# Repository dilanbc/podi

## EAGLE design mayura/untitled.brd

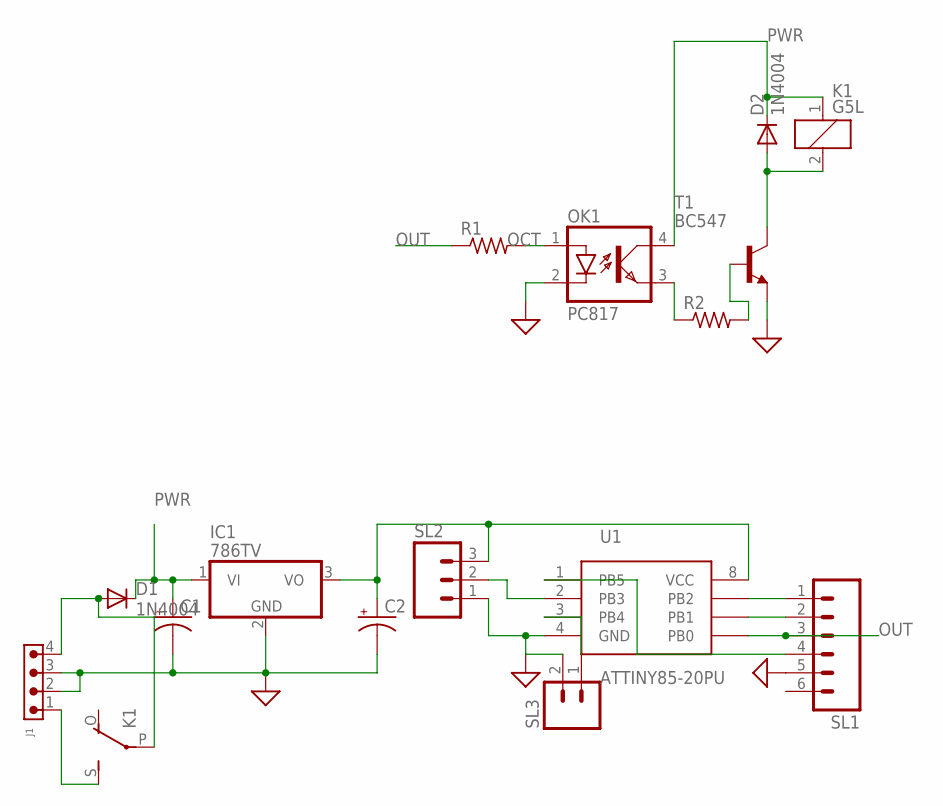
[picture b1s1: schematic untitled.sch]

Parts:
C1: CAPACITOR-PE5-10.5; E5-10,5
C2: CAPACITOR-PE2.5-5; E2,5-5
D1, D2: 1N4004; DO41-10
IC1: 786TV; TO220V
J1: 691305530004
K1: G5L; G5LE
OK1: PC817; DIL04
R1: R-US_0411/15; 0411/15
R2: R-US_0207/10; 0207/10
SL1: M06; 06P
SL2: M03; 03P
SL3: M02; 02P
T1: BC547; TO92
U1: ATTINY85-20PU; PDIP-8

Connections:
GND: C1.-, C2.-, IC1.2 (GND), J1.2, J1.3, OK1.2 (C), SL1.5, SL2.1, SL3.2, T1.1 (E), U1.4 (GND)
unnamed: D1.A, J1.4, K1.P
unnamed: SL1.1, U1.7 (PB2)
unnamed: C2.+, IC1.3 (VO), SL2.3, U1.8 (VCC)
unnamed: OK1.3 (EMIT), R2.1
unnamed: D2.A, K1.2, T1.3 (C)
unnamed: J1.1, K1.S
unnamed: R2.2, T1.2 (B)
unnamed: SL1.2, U1.6 (PB1)
unnamed: SL1.4, U1.1 (PB5)
unnamed: SL2.2, U1.2 (PB3)
unnamed: SL3.1, U1.3 (PB4)
OCT: OK1.1 (A), R1.2
OUT: R1.1, SL1.3, U1.5 (PB0)
PWR: C1.+, D1.C, D2.C, IC1.1 (VI), K1.1, OK1.4 (COL)

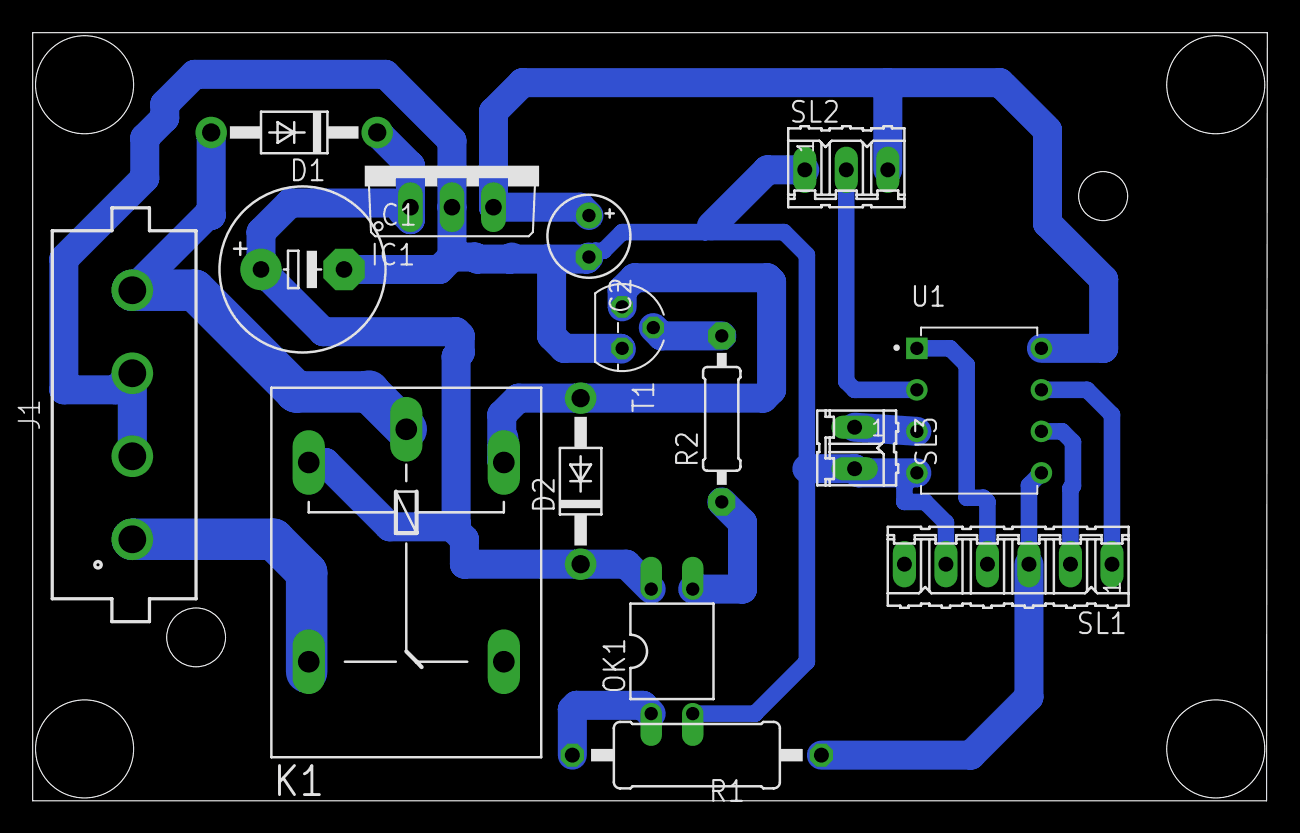
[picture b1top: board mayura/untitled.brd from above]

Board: 2 copper layers, 75.5 x 47.0 mm, 15 parts (0 on the bottom side), 15 nets.

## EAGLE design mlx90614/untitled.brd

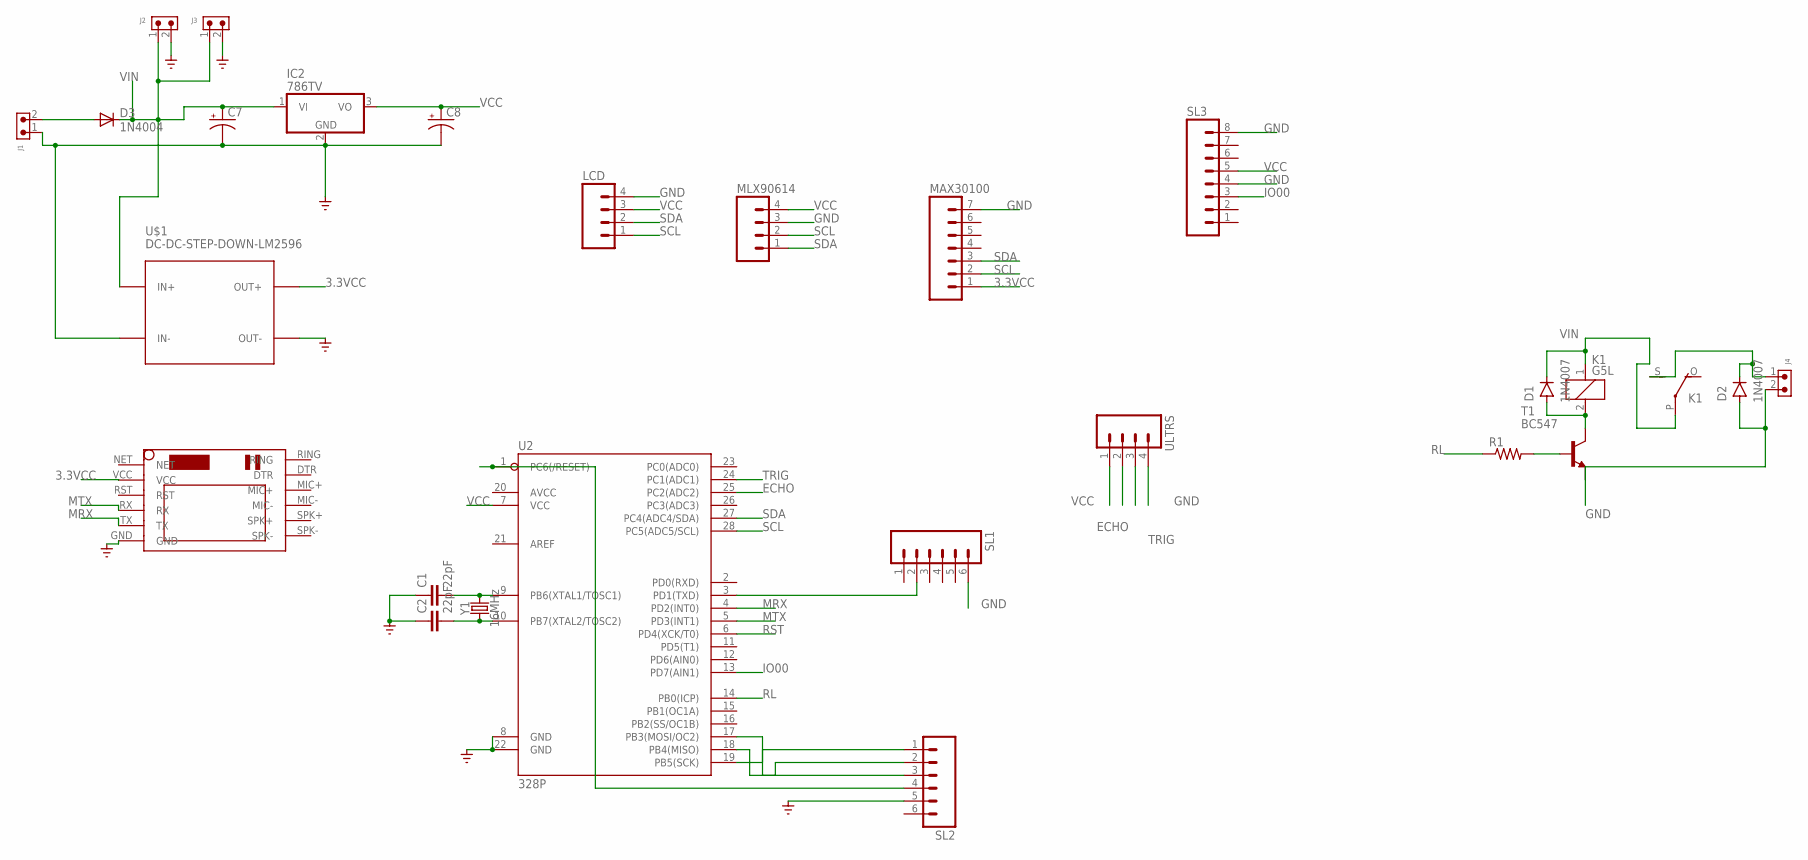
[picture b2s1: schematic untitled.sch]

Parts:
C1, C2: 22pF; CAP-PTH-2.54
C7: CAPACITOR-PE5-10.5; E5-10,5
C8: CAPACITOR-PE5-6; E5-6
D1, D2: 1N4007; DO-41
D3: 1N4004; DO41-10
IC2: 786TV; TO220V
J1, J2, J3, J4: 691305530002
K1: G5L; G5LE
LCD: M04; 04P
MAX30100: M07; 07P
MLX90614: M04; 04P
R1: R-US_0207/15; 0207/15
SL1, SL2: M06; 06P
SL3: M08; 08P
T1: BC547; TO92
U2: 328P; DIP28
U$1: DC-DC-STEP-DOWN-LM2596
U$2: SIM800LMODULE
ULTRS: M04; 04P
Y1: 16MHz; HC49US

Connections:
3.3VCC: MAX30100.1, U$1.OUT+, U$2.VCC
ECHO: U2.25 (PC2(ADC2)), ULTRS.2
GND: C1.1, C2.1, C7.-, C8.-, D2.A, IC2.2 (GND), J1.1, J2.2, J3.2, J4.2, LCD.4, MAX30100.7, MLX90614.3, SL1.6, SL2.5, SL3.4, SL3.8, T1.1 (E), U2.8 (GND), U2.22 (GND), U$1.IN-, U$1.OUT-, U$2.GND, ULTRS.4
IO00: SL3.3, U2.13 (PD7(AIN1))
MRX: U2.4 (PD2(INT0)), U$2.TX
MTX: U2.5 (PD3(INT1)), U$2.RX
unnamed: R1.2, T1.2 (B)
unnamed: C1.2, U2.9 (PB6(XTAL1/TOSC1)), Y1.2
unnamed: C2.2, U2.10 (PB7(XTAL2/TOSC2)), Y1.1
unnamed: SL1.2, U2.3 (PD1(TXD))
unnamed: D2.C, J4.1, K1.S
unnamed: D1.A, K1.2, T1.3 (C)
unnamed: SL2.4, U2.1 (PC6(/RESET))
unnamed: SL2.1, U2.19 (PB5(SCK))
unnamed: SL2.2, U2.18 (PB4(MISO))
unnamed: SL2.3, U2.17 (PB3(MOSI/OC2))
unnamed: D3.A, J1.2
RL: R1.1, U2.14 (PB0(ICP))
RST: U2.6 (PD4(XCK/T0))
SCL: LCD.1, MAX30100.2, MLX90614.2, U2.28 (PC5(ADC5/SCL))
SDA: LCD.2, MAX30100.3, MLX90614.1, U2.27 (PC4(ADC4/SDA))
TRIG: U2.24 (PC1(ADC1)), ULTRS.3
VCC: C8.+, IC2.3 (VO), LCD.3, MLX90614.4, SL3.5, U2.7 (VCC), ULTRS.1
VIN: C7.+, D1.C, D3.C, IC2.1 (VI), J2.1, J3.1, K1.1, K1.P, U$1.IN+

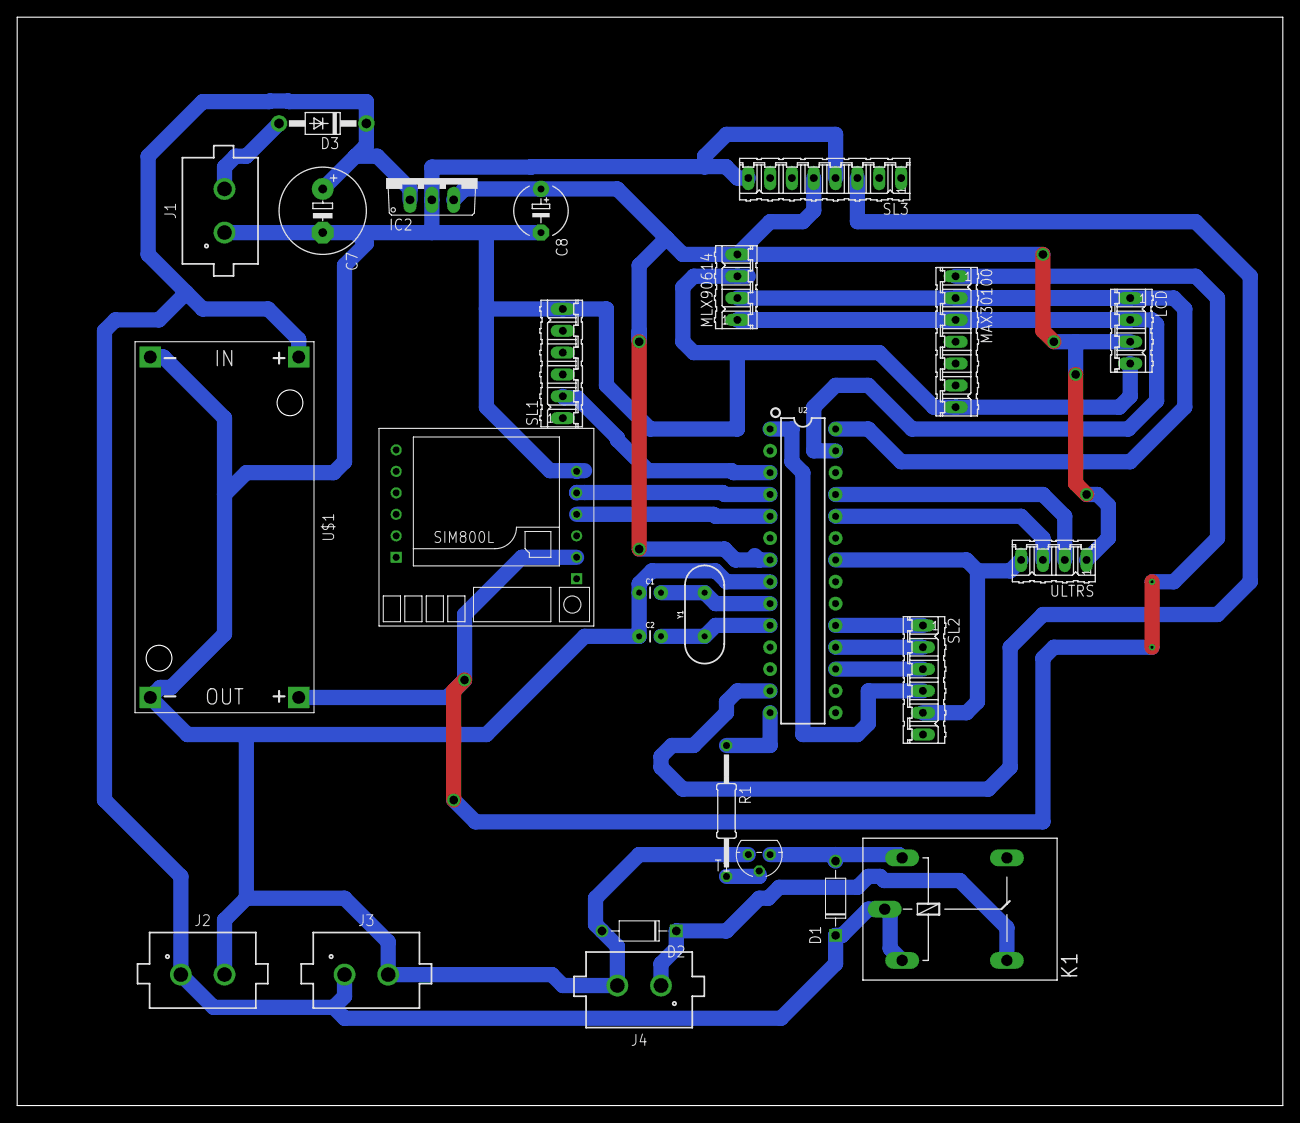
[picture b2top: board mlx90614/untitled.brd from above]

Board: 2 copper layers, 147.3 x 126.7 mm, 26 parts (0 on the bottom side), 23 nets.

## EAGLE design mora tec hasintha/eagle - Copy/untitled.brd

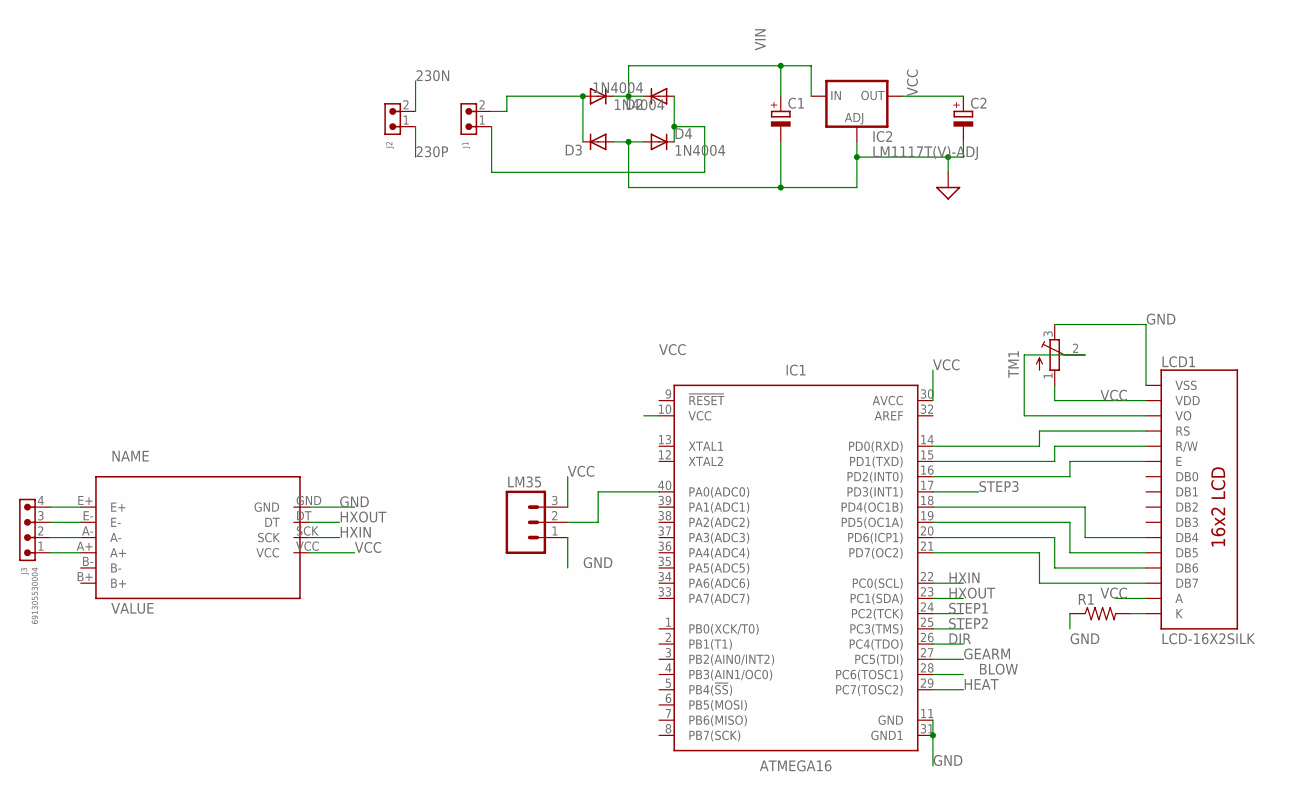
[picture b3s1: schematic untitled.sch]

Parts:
C1, C2: CPOL-EUE5-10.5; E5-10,5
D1, D2, D3, D4: 1N4004; DO41-10
IC1: ATMEGA16; DIP1587W56P254L5229H482Q40B
IC2: LM1117T(V)-ADJ; TO220V
J1, J2: 691305530002
J3: 691305530004
LCD1: LCD-16X2SILK; LCD-16X2
LM35: M03; 03P
R1: R-US_0207/9; 0207/9
TM1: TRIMPOTTC33X; TC33X
U$3: HX711A; HX711

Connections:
230N: J2.2
230P: J2.1
BLOW: IC1.28 (PC6(TOSC1))
DIR: IC1.26 (PC4(TDO))
GEARM: IC1.27 (PC5(TDI))
GND: C1.-, C2.-, D3.A, D4.A, IC1.11 (GND), IC1.31 (GND1), IC2.1 (ADJ), LCD1.1 (VSS), LM35.1, R1.1, TM1.3 (E), U$3.GND
HEAT: IC1.29 (PC7(TOSC2))
HXIN: IC1.22 (PC0(SCL)), U$3.SCK
HXOUT: IC1.23 (PC1(SDA)), U$3.DT
unnamed: D1.A, D3.C, J1.2
unnamed: D2.A, D4.C, J1.1
unnamed: J3.4, U$3.E+
unnamed: J3.3, U$3.E-
unnamed: J3.2, U$3.A-
unnamed: J3.1, U$3.A+
unnamed: IC1.21 (PD7(OC2)), LCD1.14 (DB7)
unnamed: IC1.20 (PD6(ICP1)), LCD1.13 (DB6)
unnamed: IC1.19 (PD5(OC1A)), LCD1.12 (DB5)
unnamed: IC1.18 (PD4(OC1B)), LCD1.11 (DB4)
unnamed: IC1.14 (PD0(RXD)), LCD1.4 (RS)
unnamed: IC1.15 (PD1(TXD)), LCD1.5 (R/W)
unnamed: IC1.16 (PD2(INT0)), LCD1.6 (E)
unnamed: LCD1.3 (VO), TM1.2 (S)
unnamed: LCD1.16 (K), R1.2
unnamed: IC1.40 (PA0(ADC0)), LM35.2
STEP1: IC1.24 (PC2(TCK))
STEP2: IC1.25 (PC3(TMS))
STEP3: IC1.17 (PD3(INT1))
VCC: C2.+, IC1.10 (VCC), IC1.30 (AVCC), IC2.2 (OUT), LCD1.2 (VDD), LCD1.15 (A), LM35.3, TM1.1 (A), U$3.VCC
VIN: C1.+, D1.C, D2.C, IC2.3 (IN)

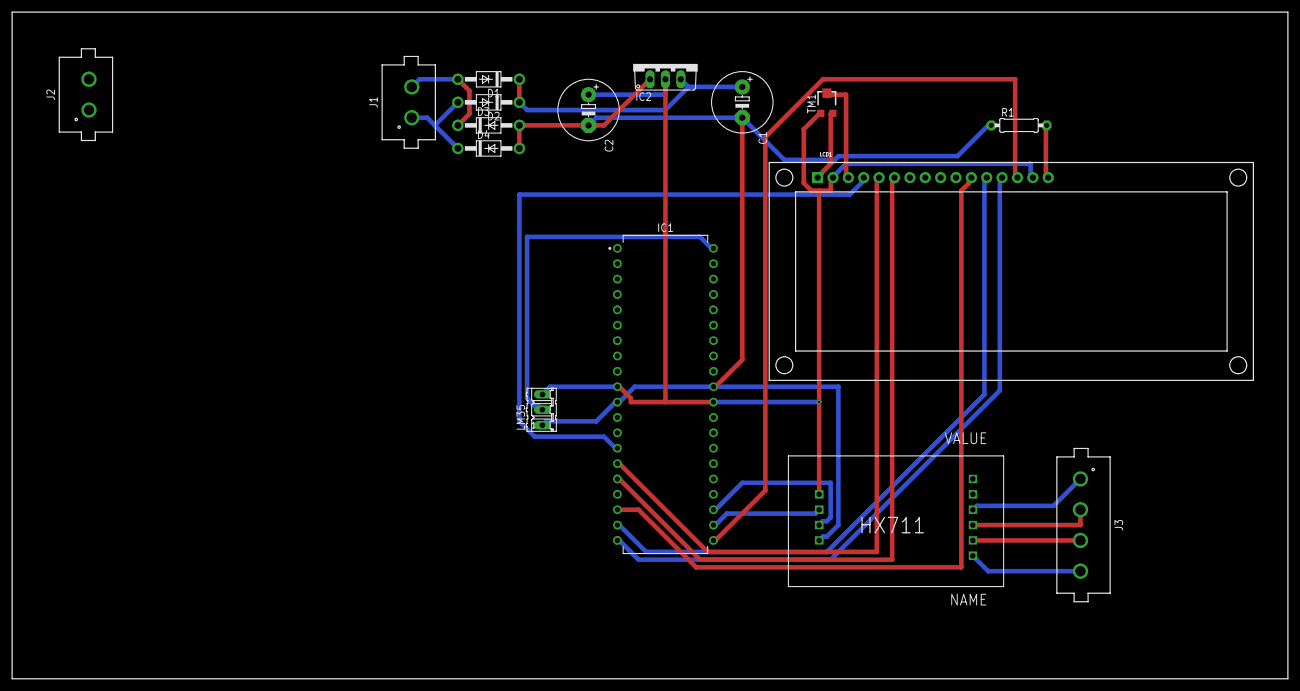
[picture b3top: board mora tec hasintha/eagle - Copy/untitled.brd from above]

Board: 2 copper layers, 210.8 x 110.2 mm, 16 parts (0 on the bottom side), 21 nets.

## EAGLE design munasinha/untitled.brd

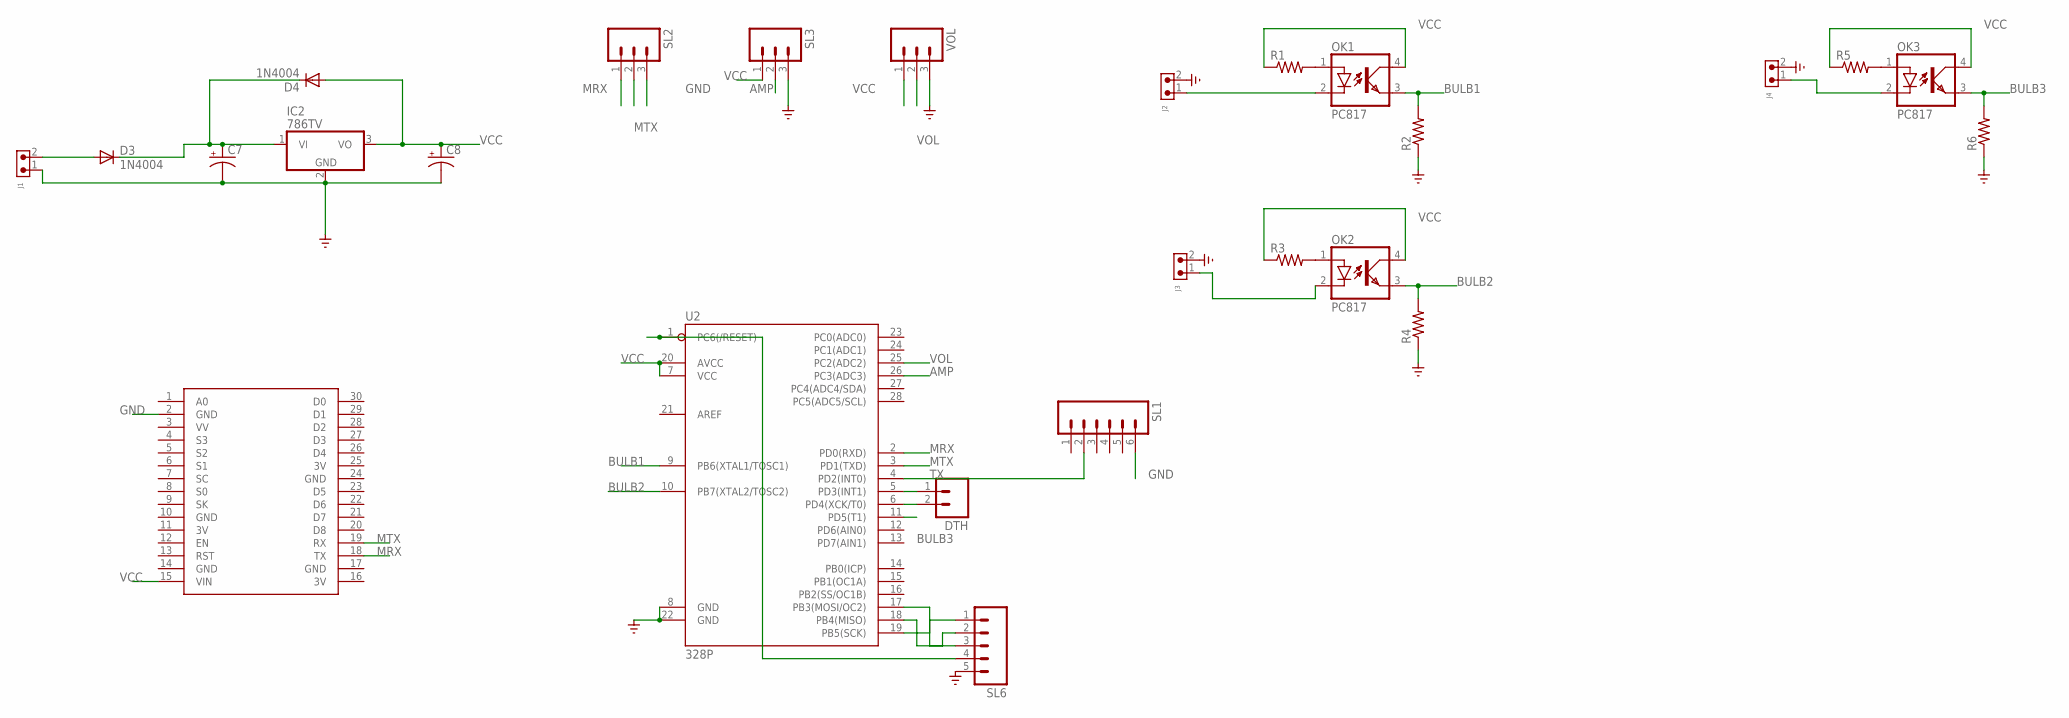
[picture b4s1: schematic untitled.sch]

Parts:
C7: CAPACITOR-PE5-10.5; E5-10,5
C8: CAPACITOR-PE5-6; E5-6
D3, D4: 1N4004; DO41-10
DTH: M02; 02P
IC2: 786TV; TO220V
J1, J2, J3, J4: 691305530002
OK1, OK2, OK3: PC817; DIL04
R1, R2, R3, R4, R5, R6: R-US_0207/10; 0207/10
SL1: M06; 06P
SL2, SL3: M03; 03P
SL6: M05; 05P
U2: 328P; DIP28
U$1: NODEMCU
VOL: M03; 03P

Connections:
3V: U$1.11 (3V), U$1.16 (3V), U$1.25 (3V)
AMP: SL3.2, U2.26 (PC3(ADC3))
BULB1: OK1.3 (EMIT), R2.2, U2.9 (PB6(XTAL1/TOSC1))
BULB2: OK2.3 (EMIT), R4.2, U2.10 (PB7(XTAL2/TOSC2))
BULB3: OK3.3 (EMIT), R6.2, U2.11 (PD5(T1))
GND: C7.-, C8.-, IC2.2 (GND), J1.1, J2.2, J3.2, J4.2, R2.1, R4.1, R6.1, SL1.6, SL2.3, SL3.3, SL6.5, U2.8 (GND), U2.22 (GND), U$1.2 (GND), U$1.10 (GND), U$1.14 (GND), U$1.17 (GND), U$1.24 (GND), VOL.3
MRX: SL2.1, U2.2 (PD0(RXD)), U$1.18 (TX)
MTX: SL2.2, U2.3 (PD1(TXD)), U$1.19 (RX)
unnamed: OK1.1 (A), R1.2
unnamed: DTH.1, U2.5 (PD3(INT1))
unnamed: DTH.2, U2.6 (PD4(XCK/T0))
unnamed: OK2.1 (A), R3.2
unnamed: OK3.1 (A), R5.2
unnamed: J2.1, OK1.2 (C)
unnamed: C7.+, D3.C, D4.C, IC2.1 (VI)
unnamed: J3.1, OK2.2 (C)
unnamed: SL6.4, U2.1 (PC6(/RESET))
unnamed: J4.1, OK3.2 (C)
unnamed: SL6.1, U2.19 (PB5(SCK))
unnamed: SL6.2, U2.18 (PB4(MISO))
unnamed: SL6.3, U2.17 (PB3(MOSI/OC2))
unnamed: D3.A, J1.2
TX: SL1.2, U2.4 (PD2(INT0))
VCC: C8.+, D4.A, IC2.3 (VO), OK1.4 (COL), OK2.4 (COL), OK3.4 (COL), R1.1, R3.1, R5.1, SL3.1, U2.7 (VCC), U2.20 (AVCC), U$1.15 (VIN), VOL.1
VOL: U2.25 (PC2(ADC2)), VOL.2

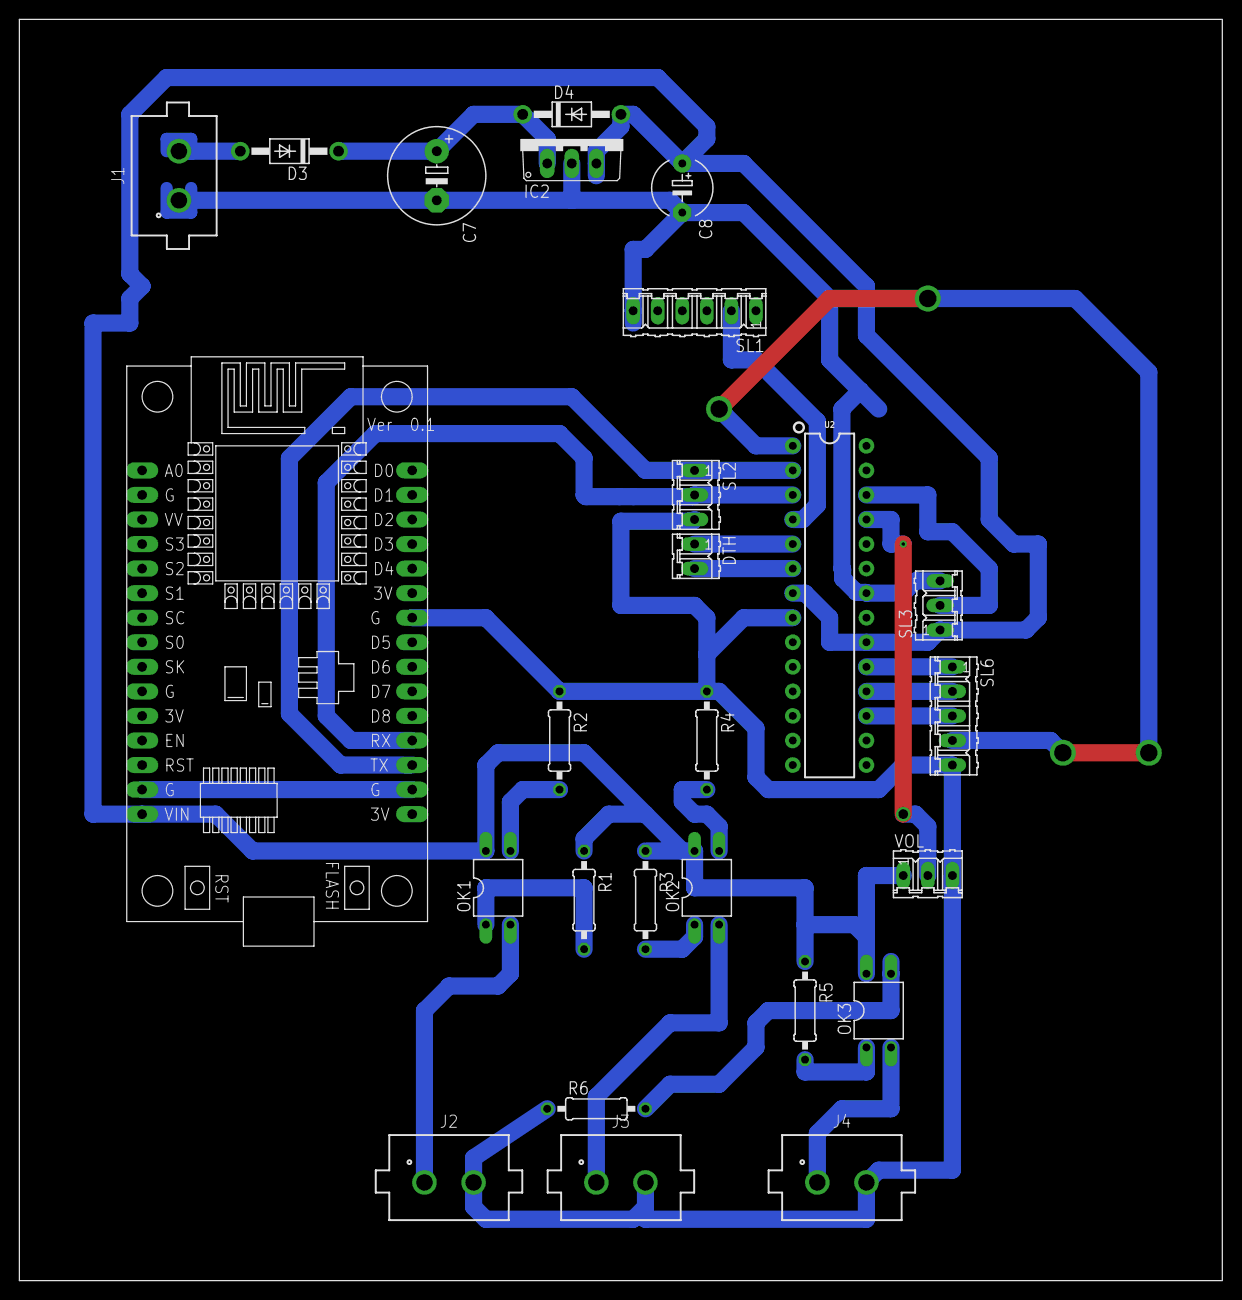
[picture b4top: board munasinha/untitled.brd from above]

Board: 2 copper layers, 124.4 x 130.5 mm, 26 parts (0 on the bottom side), 25 nets.

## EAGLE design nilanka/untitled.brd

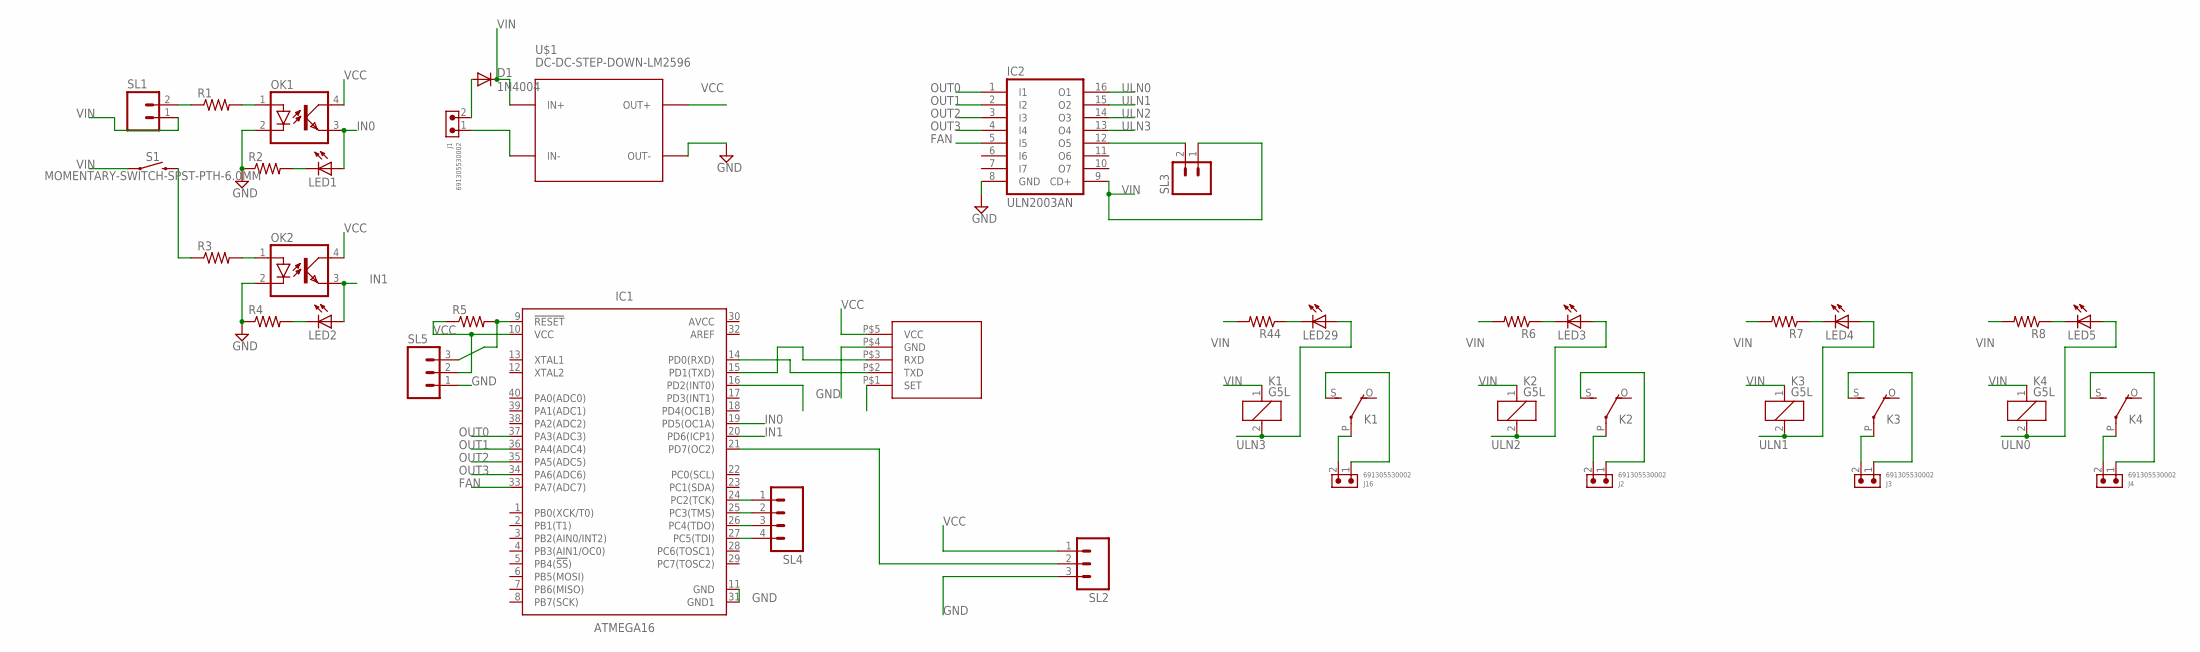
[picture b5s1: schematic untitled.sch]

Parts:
D1: 1N4004; DO41-10
IC1: ATMEGA16; DIP1587W56P254L5229H482Q40B
IC2: ULN2003AN; DIL16
J1, J2, J3, J4, J16: 691305530002
K1, K2, K3, K4: G5L; G5LE
LED1, LED2, LED3, LED4, LED5, LED29: LED5MM
OK1, OK2: PC817; DIL04
R1, R2, R3, R4, R5, R6, R7, R8, R44: R-US_0207/7; 0207/7
S1: MOMENTARY-SWITCH-SPST-PTH-6.0MM; TACTILE_SWITCH_PTH_6.0MM
SL1, SL3: M02; 02P
SL2, SL5: M03; 03P
SL4: M04; 04P
U$1: DC-DC-STEP-DOWN-LM2596
U$2: HC12

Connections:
AVCC: IC1.30 (AVCC)
FAN: IC1.33 (PA7(ADC7)), IC2.5 (I5)
GND: IC1.11 (GND), IC1.31 (GND1), IC2.8 (GND), OK1.2 (C), OK2.2 (C), R2.1, R4.1, SL2.3, SL5.1, U$1.OUT-, U$2.P$4 (GND)
IN0: IC1.19 (PD5(OC1A)), LED1.A, OK1.3 (EMIT)
IN1: IC1.20 (PD6(ICP1)), LED2.A, OK2.3 (EMIT)
unnamed: D1.A, J1.2
unnamed: R1.1, SL1.2
unnamed: OK1.1 (A), R1.2
unnamed: J2.2, K2.P
unnamed: IC1.9 (!RESET!), R5.2, SL5.3
unnamed: LED1.K (C), R2.2
unnamed: R3.1, S1.3 (2)
unnamed: OK2.1 (A), R3.2
unnamed: J2.1, K2.S
unnamed: LED3.K (C), R6.1
unnamed: LED2.K (C), R4.2
unnamed: J3.2, K3.P
unnamed: J3.1, K3.S
unnamed: LED4.K (C), R7.1
unnamed: J4.2, K4.P
unnamed: J4.1, K4.S
unnamed: LED5.K (C), R8.1
unnamed: IC1.14 (PD0(RXD)), U$2.P$2 (TXD)
unnamed: IC1.15 (PD1(TXD)), U$2.P$3 (RXD)
unnamed: IC1.21 (PD7(OC2)), SL2.2
unnamed: IC2.12 (O5), SL3.2
unnamed: IC1.24 (PC2(TCK)), SL4.1
unnamed: J1.1, U$1.IN-
unnamed: IC1.25 (PC3(TMS)), SL4.2
unnamed: IC1.26 (PC4(TDO)), SL4.3
unnamed: IC1.27 (PC5(TDI)), SL4.4
unnamed: J16.2, K1.P
unnamed: J16.1, K1.S
unnamed: LED29.K (C), R44.1
OUT0: IC1.37 (PA3(ADC3)), IC2.1 (I1)
OUT1: IC1.36 (PA4(ADC4)), IC2.2 (I2)
OUT2: IC1.35 (PA5(ADC5)), IC2.3 (I3)
OUT3: IC1.34 (PA6(ADC6)), IC2.4 (I4)
ULN0: IC2.16 (O1), K4.2, LED5.A
ULN1: IC2.15 (O2), K3.2, LED4.A
ULN2: IC2.14 (O3), K2.2, LED3.A
ULN3: IC2.13 (O4), K1.2, LED29.A
VCC: IC1.10 (VCC), OK1.4 (COL), OK2.4 (COL), R5.1, SL2.1, SL5.2, U$1.OUT+, U$2.P$5 (VCC)
VIN: D1.C, IC2.9 (CD+), K1.1, K2.1, K3.1, K4.1, R6.2, R7.2, R8.2, R44.2, S1.1, SL1.1, SL3.1, U$1.IN+

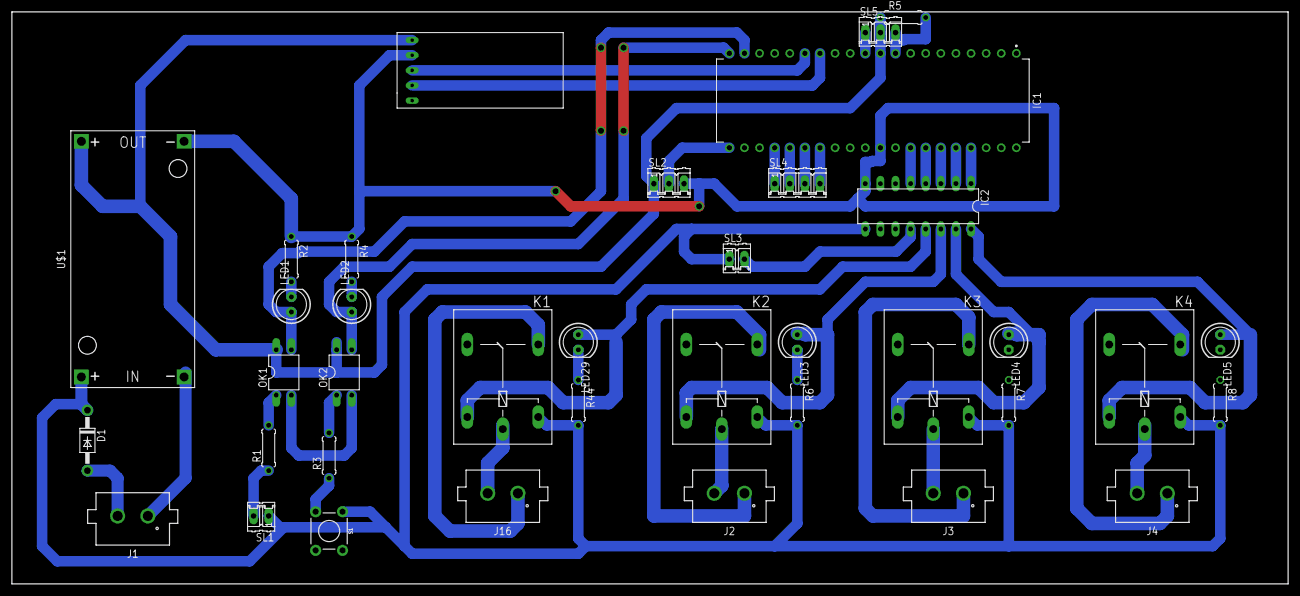
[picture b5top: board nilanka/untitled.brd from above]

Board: 2 copper layers, 214.6 x 96.2 mm, 37 parts (0 on the bottom side), 43 nets.

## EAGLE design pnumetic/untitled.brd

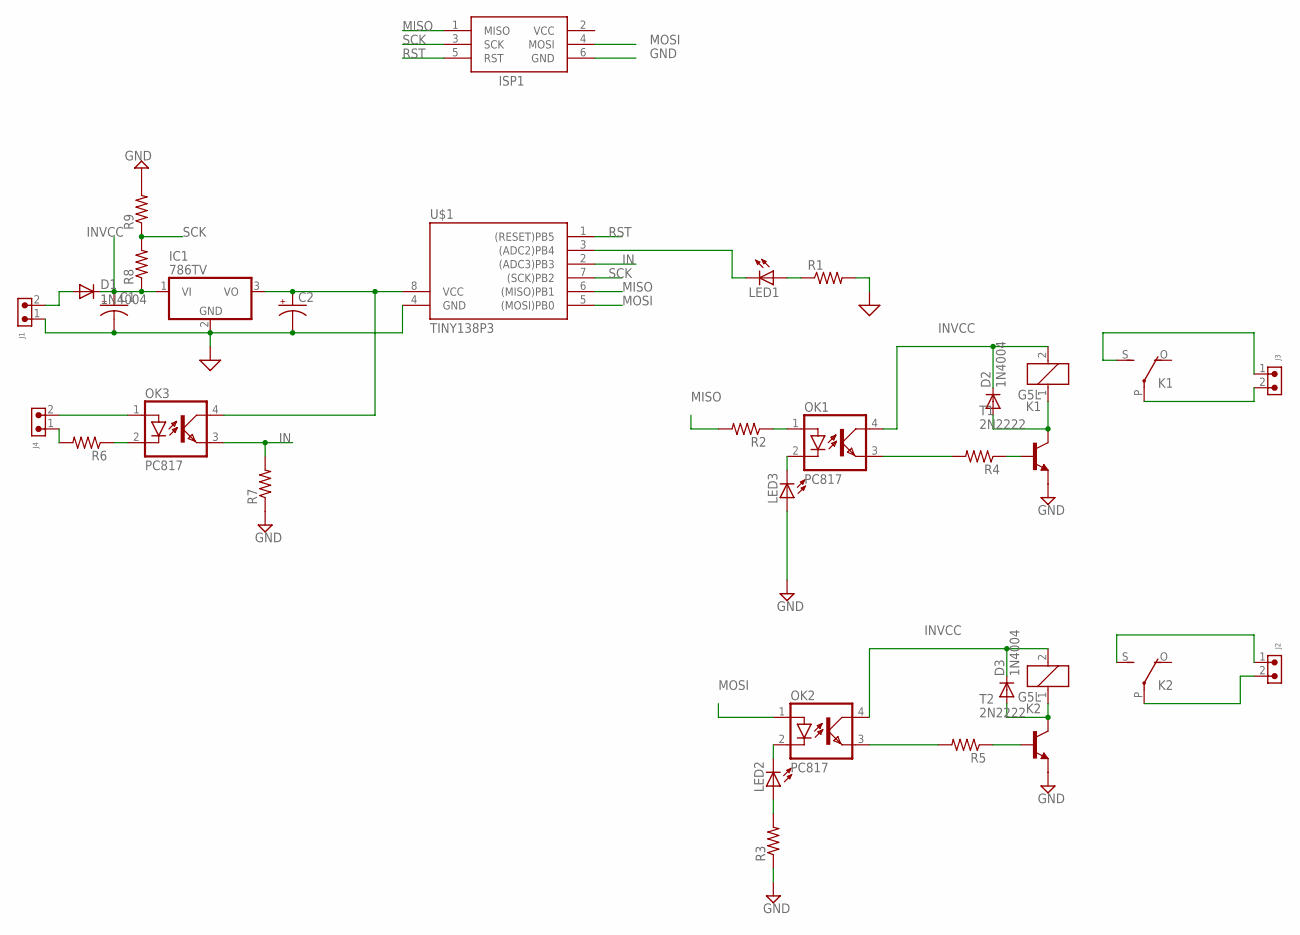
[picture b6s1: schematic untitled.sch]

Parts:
C1: CAPACITOR-PE7.5-16; E7,5-16
C2: CAPACITOR-PE2,5-6E; E2,5-6E
D1, D2, D3: 1N4004; DO41-10
IC1: 786TV; TO220V
ISP1: AVRISP-6; AVRISP
J1, J2, J3, J4: 691305530002
K1, K2: G5L; G5LE
LED1, LED2, LED3: LED5MM
OK1, OK2, OK3: PC817; DIL04
R1: R-US_0207/15; 0207/15
R2, R3, R6, R8, R9: R-US_0207/7; 0207/7
R4, R5: R-US_0207/9; 0207/9
R7: R-US_0207/12; 0207/12
T1, T2: 2N2222; TO92-EBC-OVAL
U$1: TINY138P3; DIL08

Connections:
GND: C1.-, C2.-, IC1.2 (GND), ISP1.6 (GND), J1.1, LED3.A, R1.2, R3.1, R7.1, R9.2, T1.E, T2.E, U$1.4 (GND)
IN: OK3.3 (EMIT), R7.2, U$1.2 ((ADC3)PB3)
INVCC: C1.+, D1.C, D2.C, D3.C, IC1.1 (VI), K1.2, K2.2, OK1.4 (COL), OK2.4 (COL), R8.1
MISO: ISP1.1 (MISO), R2.2, U$1.6 ((MISO)PB1)
MOSI: ISP1.4 (MOSI), OK2.1 (A), U$1.5 ((MOSI)PB0)
unnamed: LED3.K (C), OK1.2 (C)
unnamed: LED1.A, R1.1
unnamed: D1.A, J1.2
unnamed: C2.+, IC1.3 (VO), OK3.4 (COL), U$1.8 (VCC)
unnamed: LED2.A, R3.2
unnamed: OK1.1 (A), R2.1
unnamed: OK2.3 (EMIT), R5.2
unnamed: LED2.K (C), OK2.2 (C)
unnamed: R4.1, T1.B
unnamed: R5.1, T2.B
unnamed: J2.2, K2.P
unnamed: D3.A, K2.1, T2.C
unnamed: D2.A, K1.1, T1.C
unnamed: J2.1, K2.S
unnamed: J3.2, K1.P
unnamed: J3.1, K1.S
unnamed: J4.2, OK3.1 (A)
unnamed: OK3.2 (C), R6.1
unnamed: J4.1, R6.2
unnamed: OK1.3 (EMIT), R4.2
unnamed: LED1.K (C), U$1.3 ((ADC2)PB4)
RST: ISP1.5 (RST), U$1.1 ((RESET)PB5)
SCK: ISP1.3 (SCK), R8.2, R9.1, U$1.7 ((SCK)PB2)
VCC: ISP1.2 (VCC)

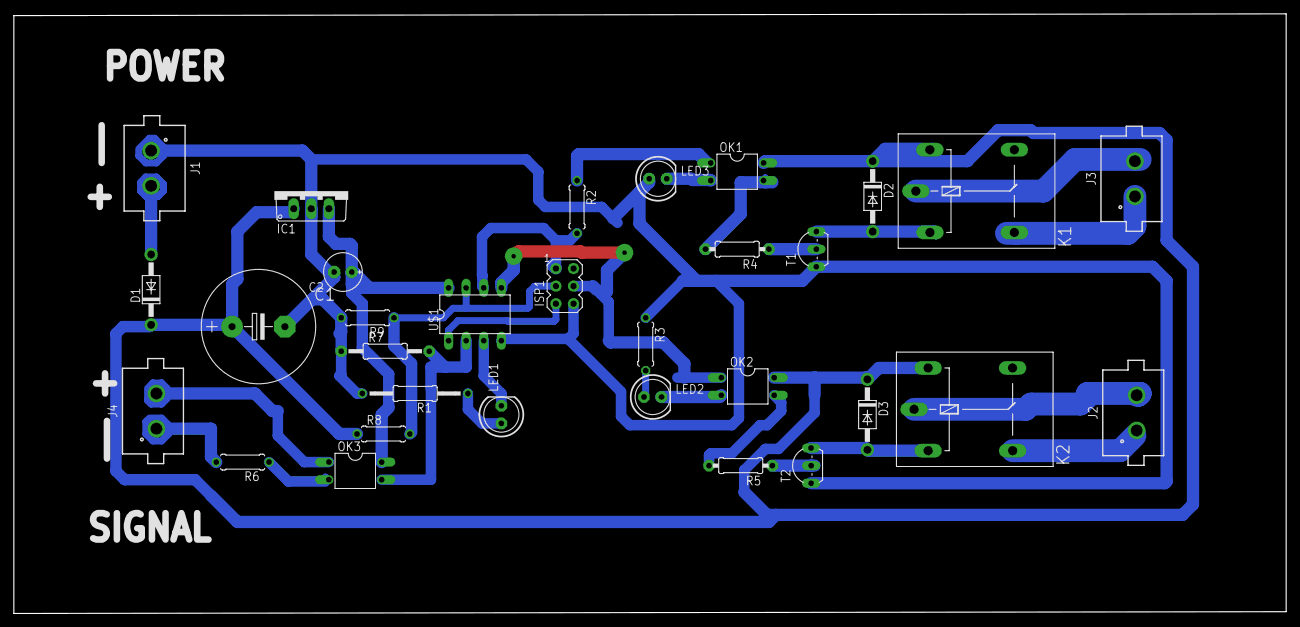
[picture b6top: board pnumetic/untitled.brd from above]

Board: 2 copper layers, 183.6 x 86.5 mm, 31 parts (0 on the bottom side), 28 nets.

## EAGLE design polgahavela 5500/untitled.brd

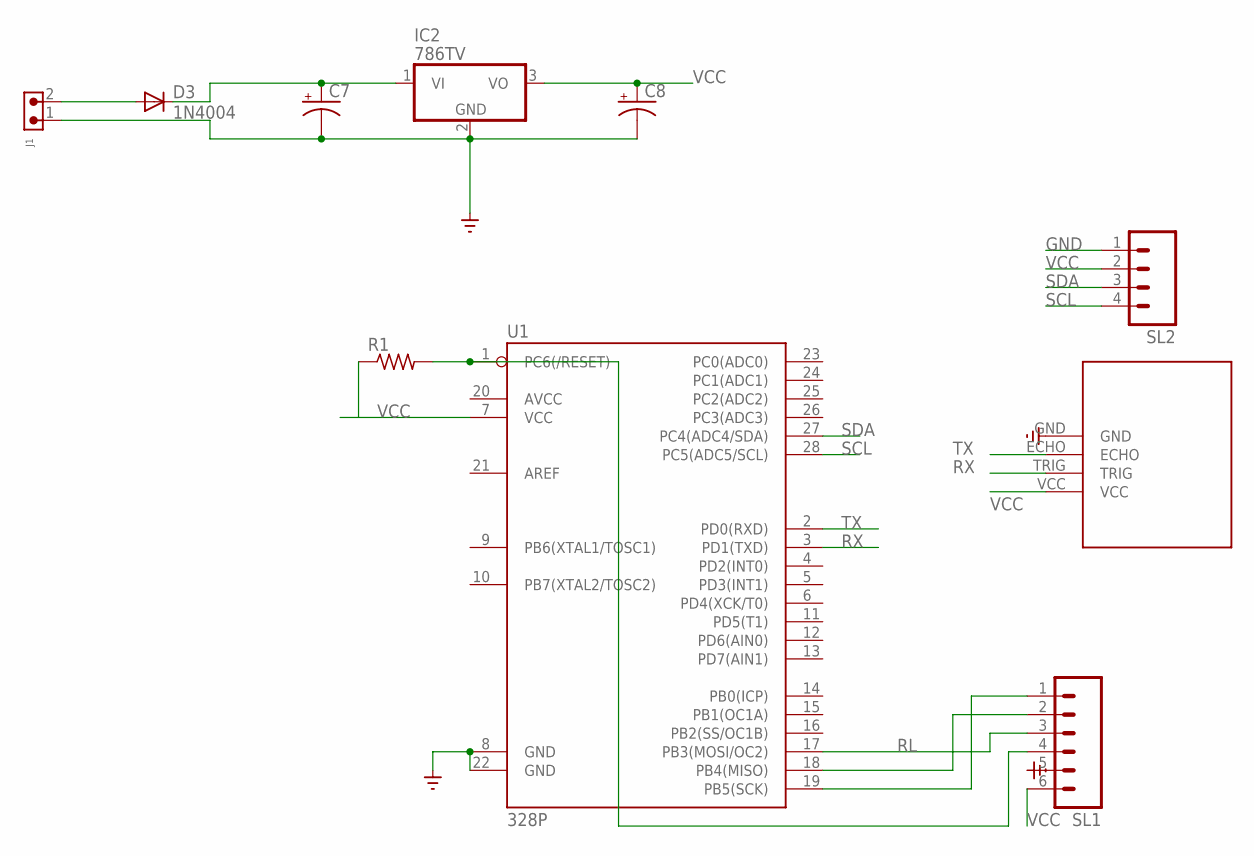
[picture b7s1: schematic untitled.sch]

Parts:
C7: CAPACITOR-PE5-10.5; E5-10,5
C8: CAPACITOR-PE5-6; E5-6
D3: 1N4004; DO41-10
IC2: 786TV; TO220V
J1: 691305530002
R1: R-US_0207/7; 0207/7
SL1: M06; 06P
SL2: M04; 04P
U1: 328P; DIP28
U$6: SRO4M

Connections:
GND: C7.-, C8.-, IC2.2 (GND), J1.1, SL1.5, SL2.1, U1.8 (GND), U1.22 (GND), U$6.GND
unnamed: D3.A, J1.2
unnamed: SL1.1, U1.19 (PB5(SCK))
unnamed: SL1.2, U1.18 (PB4(MISO))
unnamed: R1.2, SL1.4, U1.1 (PC6(/RESET))
PWR: C7.+, D3.C, IC2.1 (VI)
RL: SL1.3, U1.17 (PB3(MOSI/OC2))
RX: U1.3 (PD1(TXD)), U$6.TRIG
SCL: SL2.4, U1.28 (PC5(ADC5/SCL))
SDA: SL2.3, U1.27 (PC4(ADC4/SDA))
TX: U1.2 (PD0(RXD)), U$6.ECHO
VCC: C8.+, IC2.3 (VO), R1.1, SL1.6, SL2.2, U1.7 (VCC), U$6.VCC

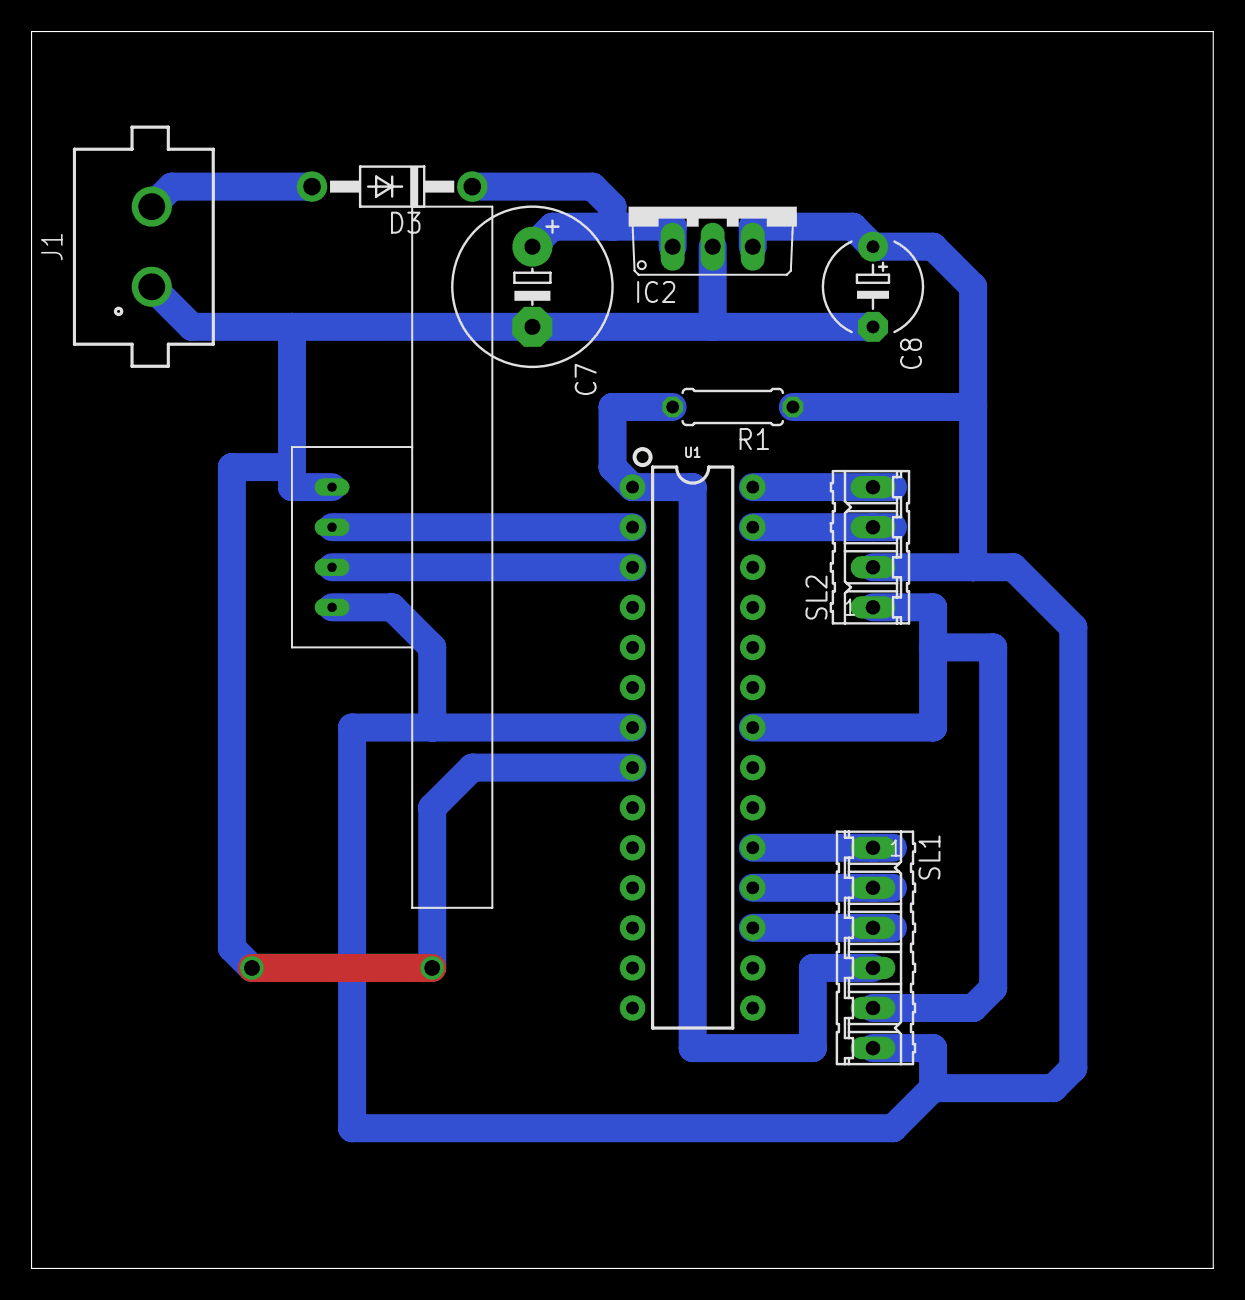
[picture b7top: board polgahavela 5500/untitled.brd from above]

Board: 2 copper layers, 74.9 x 78.4 mm, 10 parts (0 on the bottom side), 12 nets.

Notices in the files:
parts and their libraries:
Wurth_Connectors_WR-TBL Pluggable Connec: Copyright: Würth Elektronik
SparkFun-IC-Microcontroller: Licensing: Creative Commons ShareAlike 4.0 International - https://creativecommons.org/licenses/by-sa/4.0
